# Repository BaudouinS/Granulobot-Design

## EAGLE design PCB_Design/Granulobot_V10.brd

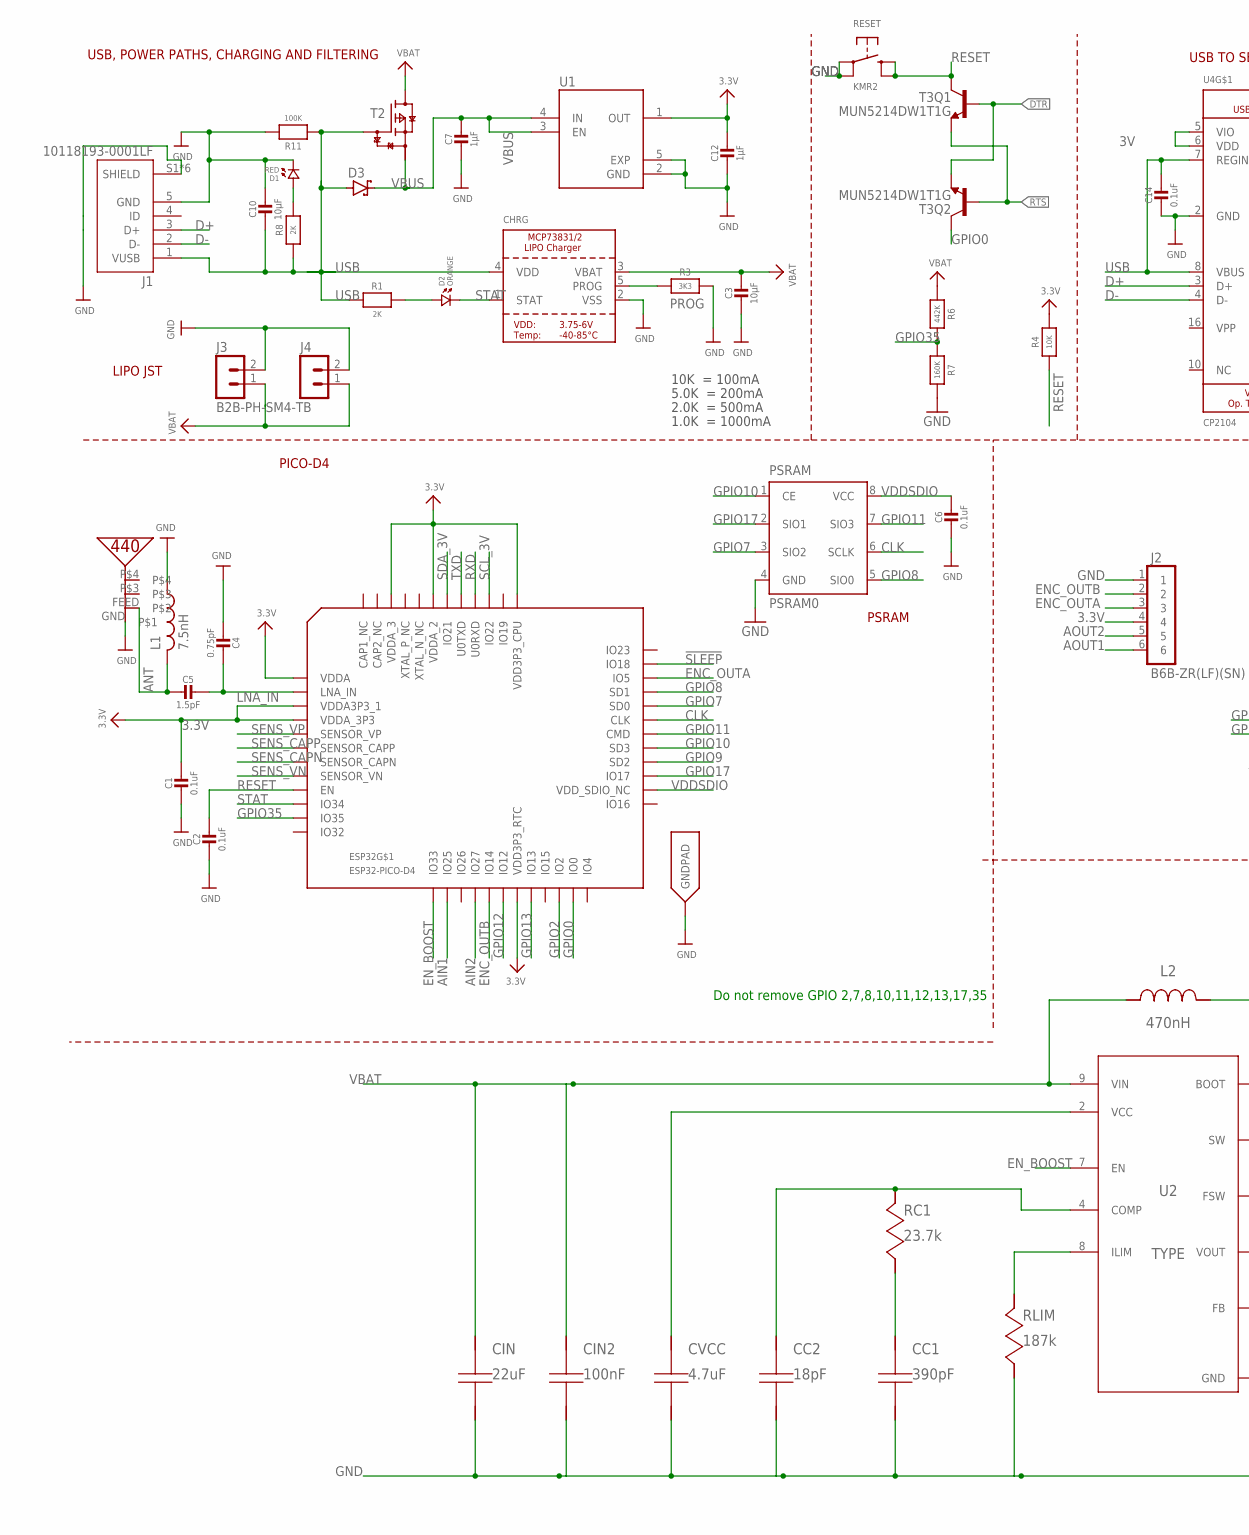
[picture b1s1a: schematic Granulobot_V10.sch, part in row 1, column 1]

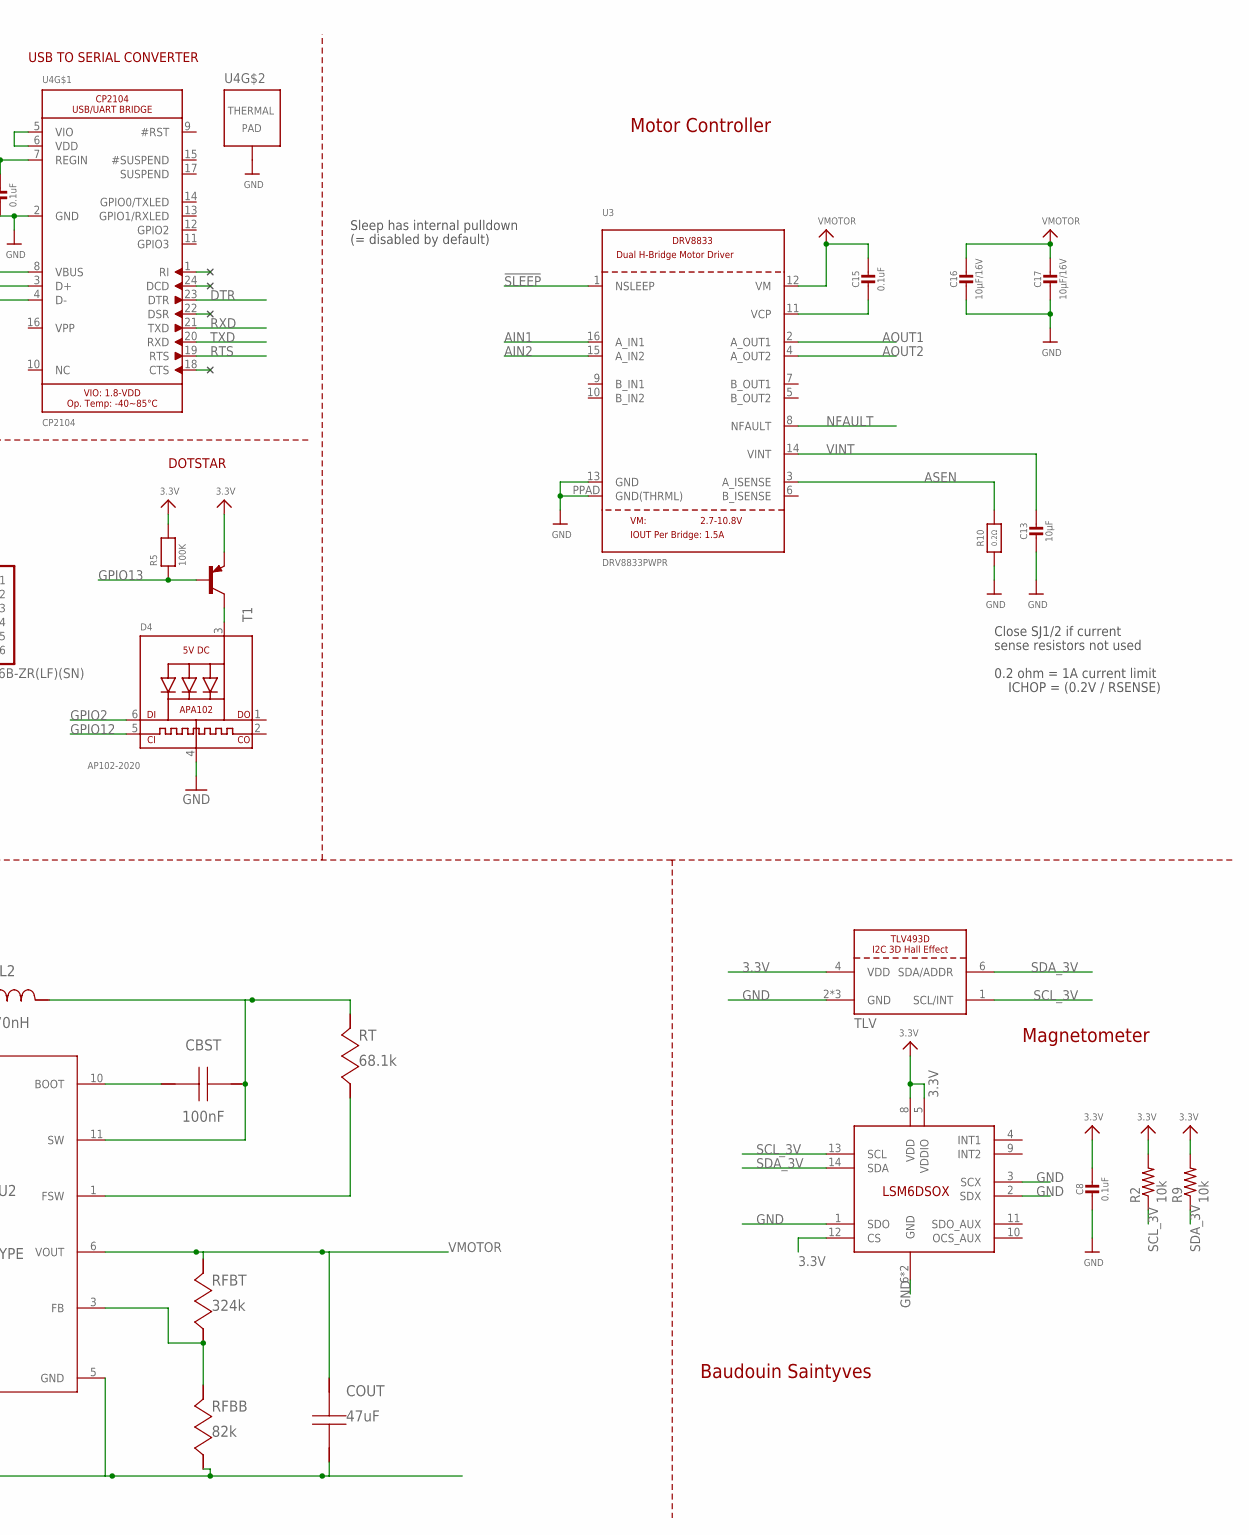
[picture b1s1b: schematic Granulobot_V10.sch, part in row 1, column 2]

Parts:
ANT: PRO-OB-440
C1, C2, C6, C14: 0.1uF; _0402MP; MPN MC0402X104K250CT
C3, C10: 10µF; _0603MP; MPN CL10A106KP8NNNC
C4: 0.75pF; _0402MP; MPN GJM1555C1HR75BB01D
C5: 1.5pF; _0402MP; MPN C1005C0G1H1R5B050BA
C7, C12: 1µF; _0402MP; MPN GRT155R70J105KE01D.
C8: 0.1uF; 0603-NO; MPN MCSH18B104K250CT
C13: 10µF; 0805-NO; MPN LMK212BJ106KG-T
C15: 0.1uF; 0805-NO; MPN MCSH21B104K100CT
C16, C17: 10µF/16V; 0805-NO; MPN CC0805KKX5R8BB106
CBST: 100nF; 0402; MPN MC0402X104K250CT
CC1: 390pF; 0402; MPN MC0402B391K250CT
CC2: 18pF; 01005; MPN GRM0225C1E180GA02L
CHRG: TP4065-4.2V-SOT25-R; SOT23-5
CIN: 22uF; 0805; MPN C1210C224J3GACTU
CIN2: 100nF; 0402; MPN MC0402X104K250CT
COUT: 47uF; 1206; MPN C0603C474K4PACTU
CVCC: 4.7uF; 0402_065; MPN JMK105BBJ475MV-F
D1: RED; 0402.LED; MPN 150040SS73220
D2: ORANGE; 0402.LED; MPN 5988A30107F
D3: BAT60J; SOD323_ST; MPN BAT60JFILM
D4: AP102-2020; MICROBUILDER_APA102_2020
ESP32: ESP32-PICO-D4; PICO-D4-QFN48
J1: 10118193-0001LF; FCI_10118193-0001LF
J2: B6B-ZR(LF)(SN); JST_B6B-ZR(LF)(SN)
J3, J4: B2B-PH-SM4-TB; MPN B2B-PH-SM4-TB(LF)(SN)
L1: 7.5nH; RESC0402_N; MPN ELJ-QF7N5JF
L2: 470nH; IHLP-1212AE; MPN IHLP1212AEERR47M11
LSM6: LSM6DSOX; LGA-14L
PSRAM: PSRAM0; SOP8
R1, R8: 2K; _0402MP; MPN ERJ-2RKF2001X
R2, R9: 10k; R0603; MPN NRC-AS06F1002TRF
R3: 3K3; _0402MP; MPN ERJ-2RKF3301X
R4: 10K; _0402MP; MPN ERJ-2RKF1002X
R5, R11: 100K; _0402MP; MPN MCWR04X1003FTL
R6: 442K; _0402MP; MPN ERJ-2RKF4423X
R7: 160K; _0402MP; MPN CRCW0402160KFKED
R10: 0.2Ω; _1206; MPN KDV12FR200ET
RC1: 23.7k; 0201
RESET: KMR2; BTN_KMR2_4.6X2.8; MPN KMR231G LFS
RFBB: 82k; 0603; MPN NRC-AS06F8202TRF
RFBT: 324k; 0402; MPN ERJ-2RKF3243X
RLIM: 187k; 0402; MPN ERJ-2RKF1873X
RT: 68.1k; 0201; MPN RC0201FR-0768K1L
T1: TINYPICO-PNPAMB; SOT883(B)
T2: TINYPICO-P-FETKMB; SOT883(B)
T3: MUN5214DW1T1G; DUAL_NPN_SC70-6; MPN MUN5214DW1T1G
TLV: TLV493D; SOT23-6; MPN TLV493DA1B6HTSA2
U1: NCP170AMX300TCG; VREG_NCP170AMX300TCG; MPN NCP170AMX300TCG
U2: Value; RNR0011A
U3: DRV8833PWPR; HTSSOP16; MPN DRV8833PWPR
U4: CP2104; MICROBUILDER_QFN24_4MM_SMSC; MPN CP2104-F03-GMR

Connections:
3.3V: C1.1, C8.1, C12.1, ESP32.1 (VDDA), ESP32.3 (VDDA3P3_1), ESP32.4 (VDDA_3P3), ESP32.19 (VDD3P3_RTC), ESP32.37 (VDD3P3_CPU), ESP32.43 (VDDA_2), ESP32.46 (VDDA_3), J2.4, LSM6.5 (VDDIO), LSM6.8 (VDD), LSM6.12 (CS), R2.2, R4.2, R5.2, R9.2, T1.2 (E), TLV.4 (VDD), U1.1 (OUT)
3V: U4.5 (VIO), U4.6 (VDD)
!SLEEP: ESP32.35 (IO18), U3.1 (NSLEEP)
AIN1: ESP32.14 (IO25), U3.16 (A_IN1)
AIN2: ESP32.16 (IO27), U3.15 (A_IN2)
ANT: ANT.FEED, C5.2, L1.2
AOUT1: J2.6, U3.2 (A_OUT1)
AOUT2: J2.5, U3.4 (A_OUT2)
ASEN: R10.2, U3.3 (A_ISENSE)
CLK: ESP32.31 (CLK), PSRAM.6 (SCLK)
D+: J1.3 (D+), U4.3 (D+)
D-: J1.2 (D-), U4.4 (D-)
DTR: T3.1 (E), T3.5 (B), U4.23 (DTR)
ENC_OUTA: ESP32.34 (IO5), J2.3
ENC_OUTB: ESP32.17 (IO14), J2.2
EN_BOOST: ESP32.13 (IO33), U2.7 (EN)
GND: ANT.GND, C1.2, C2.2, C3.2, C4.2, C6.2, C7.2, C8.2, C10.1, C12.2, C13.2, C14.2, C16.2, C17.2, CC1.2, CC2.2, CHRG.2 (VSS), CIN.2, CIN2.2, COUT.2, CVCC.2, D1.P$2 (2), D4.4 (GND), ESP32.EXP (GNDPAD), J1.5 (GND), J1.S1 (SHIELD), J1.S2 (SHIELD), J1.S3 (SHIELD), J1.S4 (SHIELD), J1.S5 (SHIELD), J1.S6 (SHIELD), J2.1, J3.2, J4.2, L1.1, LSM6.1 (SDO), LSM6.2 (SDX), LSM6.3 (SCX), LSM6.6 (GND), LSM6.7 (GND), PSRAM.4 (GND), R3.2, R7.2, R10.1, R11.2, RESET.A, RESET.A' (P1), RFBB.2, RLIM.2, TLV.2 (GND), TLV.3 (GND), TLV.5 (GND), U1.2 (GND), U1.5 (EXP), U2.5 (GND), U3.13 (GND), U3.PPAD (GND(THRML)), U4.2 (GND), U4.THERM (TP)
GPIO0: ESP32.23 (IO0), T3.6 (C)
GPIO2: D4.6 (DI), ESP32.22 (IO2)
GPIO7: ESP32.32 (SD0), PSRAM.3 (SIO2)
GPIO8: ESP32.33 (SD1), PSRAM.5 (SIO0)
GPIO9: ESP32.28 (SD2)
GPIO10: ESP32.29 (SD3), PSRAM.1 (CE)
GPIO11: ESP32.30 (CMD), PSRAM.7 (SIO3)
GPIO12: D4.5 (CKI), ESP32.18 (IO12)
GPIO13: ESP32.20 (IO13), R5.1, T1.1 (B)
GPIO17: ESP32.27 (IO17), PSRAM.2 (SIO1)
GPIO35: ESP32.11 (IO35), R6.2, R7.1
LNA_IN: C4.1, C5.1, ESP32.2 (LNA_IN)
unnamed: D1.P$1 (1), R8.2
unnamed: D2.P$1 (1), R1.2
unnamed: D4.3 (VDD), T1.3 (C)
unnamed: C15.2, U3.11 (VCP)
unnamed: RFBB.1, RFBT.2, U2.3 (FB)
unnamed: RLIM.1, U2.8 (ILIM)
unnamed: CBST.1, U2.10 (BOOT)
unnamed: CBST.2, L2.2, RT.1, U2.11 (SW)
unnamed: CVCC.1, U2.2 (VCC)
unnamed: CC1.1, RC1.2
unnamed: CC2.1, RC1.1, U2.4 (COMP)
unnamed: RT.2, U2.1 (FSW)
NFAULT: U3.8 (NFAULT)
PROG: CHRG.5 (PROG), R3.1
RESET: C2.1, ESP32.9 (EN), R4.1, RESET.B (S), RESET.B' (S1), T3.3 (C)
RTS: T3.2 (B), T3.4 (E), U4.19 (RTS)
RXD: ESP32.40 (U0RXD), U4.21 (TXD)
SCL_3V: ESP32.39 (IO22), LSM6.13 (SCL), R2.1, TLV.1 (SCL/INT)
SDA_3V: ESP32.42 (IO21), LSM6.14 (SDA), R9.1, TLV.6 (SDA/ADDR)
SENS_CAPN: ESP32.7 (SENSOR_CAPN)
SENS_CAPP: ESP32.6 (SENSOR_CAPP)
SENS_VN: ESP32.8 (SENSOR_VN)
SENS_VP: ESP32.5 (SENSOR_VP)
STAT: CHRG.1 (STAT), D2.P$2 (2), ESP32.10 (IO34)
TXD: ESP32.41 (U0TXD), U4.20 (RXD)
USB: C10.2, C14.1, CHRG.4 (VDD), D3.A, J1.1 (VUSB), R1.1, R8.1, R11.1, T2.1 (G), U4.7 (REGIN), U4.8 (VBUS)
VBAT: C3.1, CHRG.3 (VBAT), CIN.1, CIN2.1, J3.1, J4.1, L2.1, R6.1, T2.3 (D), U2.9 (VIN)
VBUS: C7.1, D3.C, T2.2 (S), U1.3 (EN), U1.4 (IN)
VDDSDIO: C6.1, ESP32.26 (VDD_SDIO_NC), PSRAM.8 (VCC)
VINT: C13.1, U3.14 (VINT)
VMOTOR: C15.1, C16.1, C17.1, COUT.1, RFBT.1, U2.6 (VOUT), U3.12 (VM)

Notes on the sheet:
USB, POWER PATHS, CHARGING AND FILTERING
USB TO SERIAL CONVERTER
PICO-D4
10K = 100mA
5.0K = 200mA
2.0K = 500mA
1.0K = 1000mA
PSRAM
DOTSTAR
Close SJ1/2 if current
sense resistors not used
0.2 ohm = 1A current limit
ICHOP = (0.2V / RSENSE)
Sleep has internal pulldown
(= disabled by default)
Motor Controller
Magnetometer
LIPO JST
Do not remove GPIO 2,7,8,10,11,12,13,17,35
Baudouin Saintyves

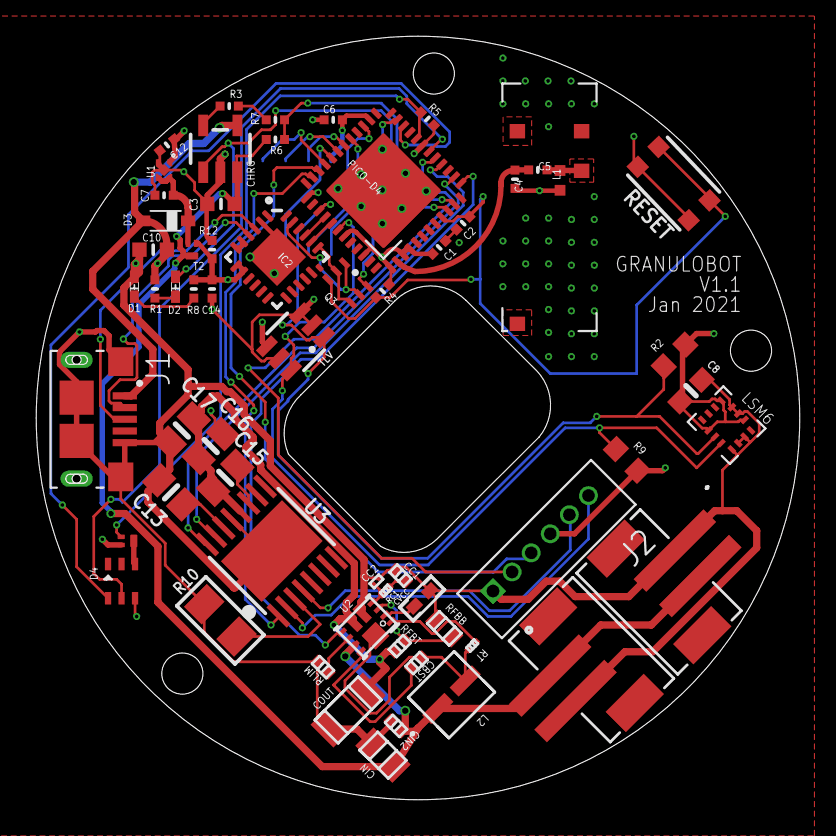
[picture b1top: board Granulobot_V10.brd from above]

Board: 4 copper layers, 42.4 x 42.4 mm, 62 parts (1 on the bottom side), 54 nets.

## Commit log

2023-02-26 Create repository with V18
    old version, V21 to come
2023-03-20 Most Recent STL files

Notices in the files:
parts and their libraries:
microbuilder: This work is placed in the public domain, and may be freely used for commercial and non-commercial work with the following conditions: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
